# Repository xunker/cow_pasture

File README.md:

# The Cow Pasture: Various boards and add-ons for the Macintosh LC and variants

## [Cow-Flipper](cow-flipper/README.md)

An adapter to flip the LC internal SCSI port by 180-degrees so devices like the original BlueSCSI can be plugged in with the OEM cable.

## [Stealth Cow](stealth-cow)

Adapter for dual-disk-drive LCs, so they can have an internal BlueSCSI drive while keeping both floppy drives. A work-in-progess.

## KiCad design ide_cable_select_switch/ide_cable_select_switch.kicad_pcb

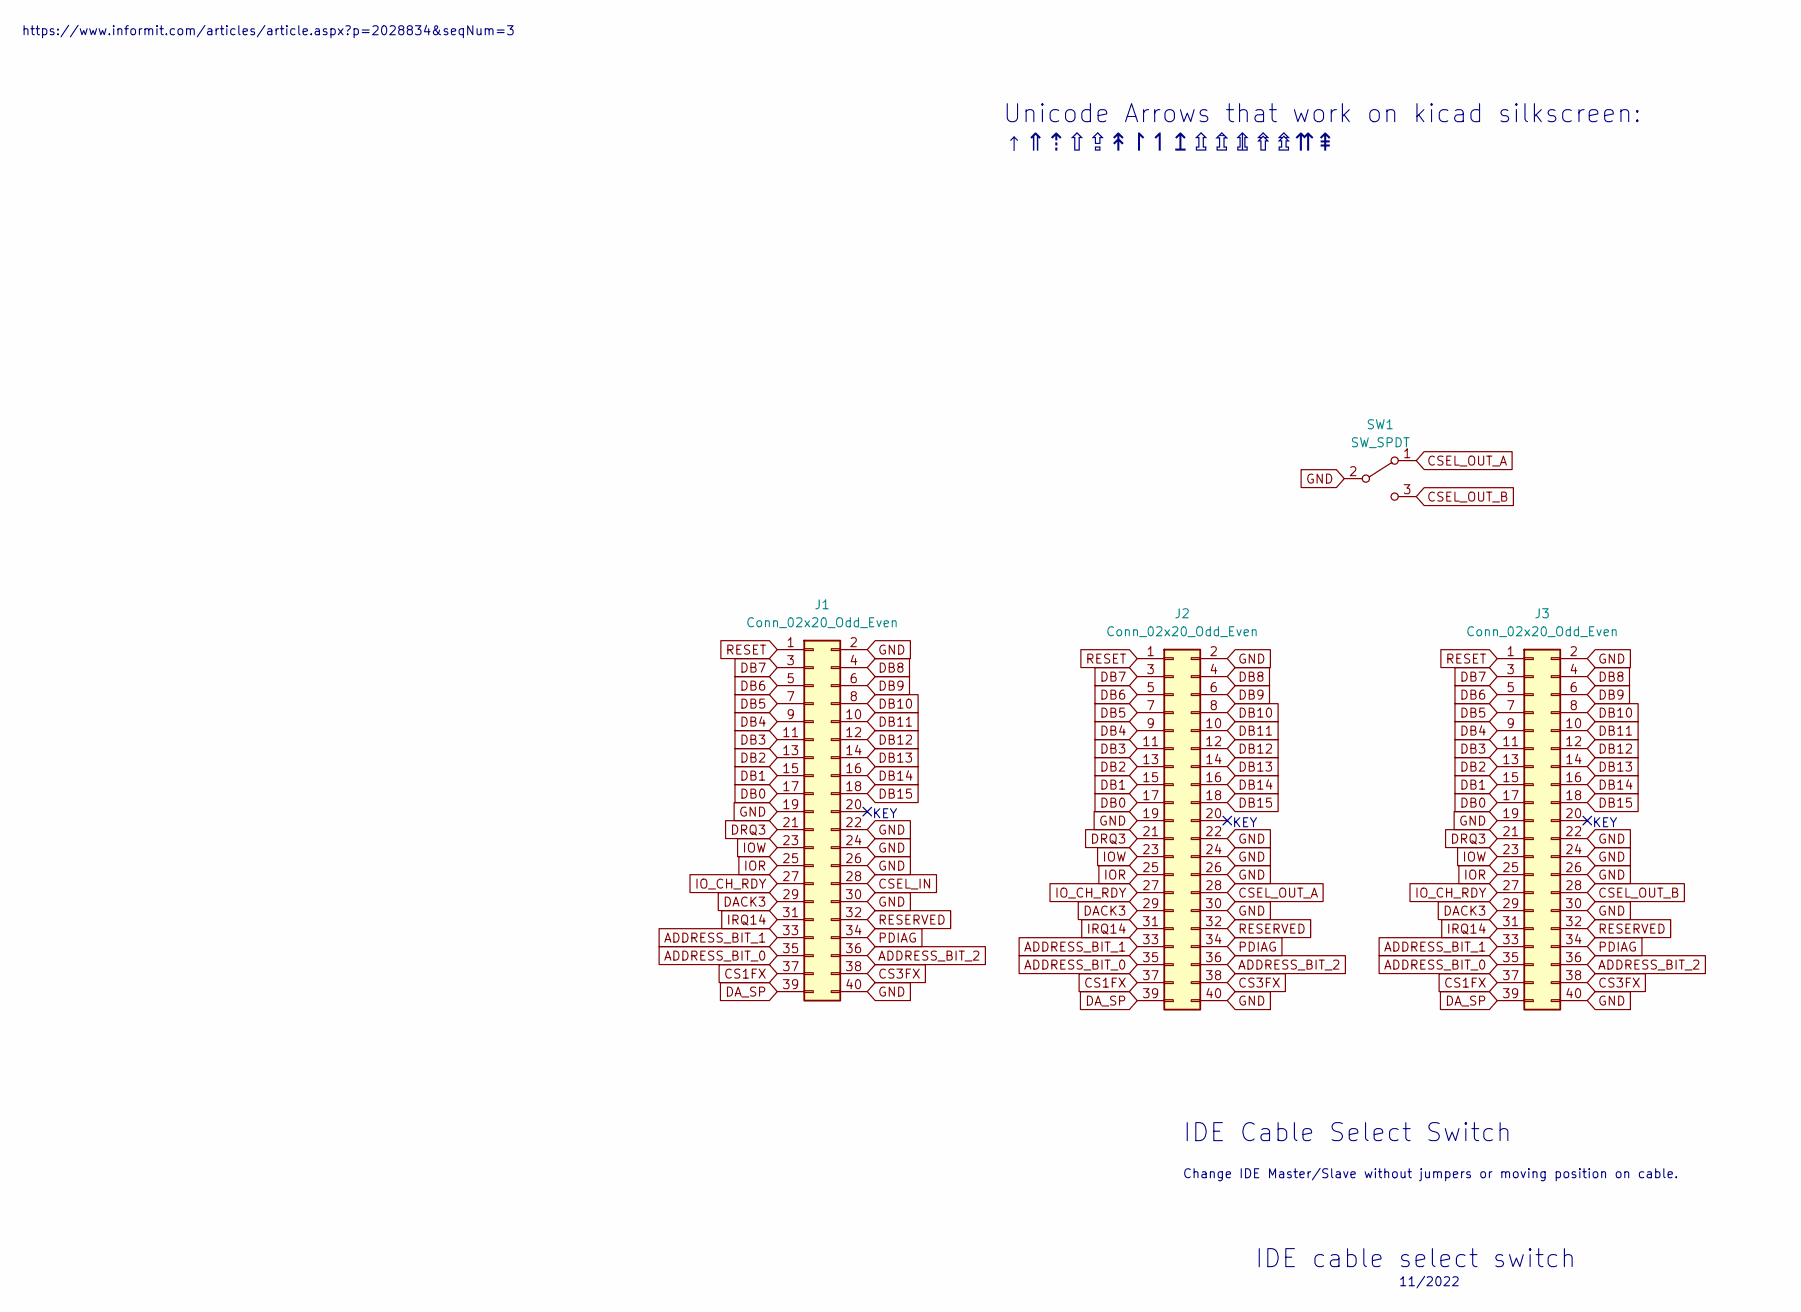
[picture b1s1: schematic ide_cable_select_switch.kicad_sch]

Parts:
J1, J2, J3: Conn_02x20_Odd_Even; IDE_ATA_Male_2x20_P2.54mm_Vertical_SMD
SW1: SW_SPDT; PinHeader_1x03_P2.54mm_Vertical

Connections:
ADDRESS_BIT_0: J1.35, J2.35, J3.35
ADDRESS_BIT_1: J1.33, J2.33, J3.33
ADDRESS_BIT_2: J1.36, J2.36, J3.36
CS1FX: J1.37, J2.37, J3.37
CS3FX: J1.38, J2.38, J3.38
CSEL_IN: J1.28
CSEL_OUT_A: J2.28, SW1.1 (A)
CSEL_OUT_B: J3.28, SW1.3 (C)
DACK3: J1.29, J2.29, J3.29
DA_SP: J1.39, J2.39, J3.39
DB0: J1.17, J2.17, J3.17
DB1: J1.15, J2.15, J3.15
DB2: J1.13, J2.13, J3.13
DB3: J1.11, J2.11, J3.11
DB4: J1.9, J2.9, J3.9
DB5: J1.7, J2.7, J3.7
DB6: J1.5, J2.5, J3.5
DB7: J1.3, J2.3, J3.3
DB8: J1.4, J2.4, J3.4
DB9: J1.6, J2.6, J3.6
DB10: J1.8, J2.8, J3.8
DB11: J1.10, J2.10, J3.10
DB12: J1.12, J2.12, J3.12
DB13: J1.14, J2.14, J3.14
DB14: J1.16, J2.16, J3.16
DB15: J1.18, J2.18, J3.18
DRQ3: J1.21, J2.21, J3.21
GND: J1.2, J1.19, J1.22, J1.24, J1.26, J1.30, J1.40, J2.2, J2.19, J2.22, J2.24, J2.26, J2.30, J2.40, J3.2, J3.19, J3.22, J3.24, J3.26, J3.30, J3.40, SW1.2 (B)
IOR: J1.25, J2.25, J3.25
IOW: J1.23, J2.23, J3.23
IO_CH_RDY: J1.27, J2.27, J3.27
IRQ14: J1.31, J2.31, J3.31
PDIAG: J1.34, J2.34, J3.34
RESERVED: J1.32, J2.32, J3.32
RESET: J1.1, J2.1, J3.1

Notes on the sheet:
KEY
Unicode Arrows that work on kicad silkscreen: ↑⇑⇡︎⇧⇪↟↾↿↥⇫⇬⇭⇮⇯⇈⇞
IDE cable select switch
IDE Cable Select Switch
Change IDE Master/Slave without jumpers or moving position on cable.
11/2022
https://www.informit.com/articles/article.aspx?p=2028834&seqNum=3

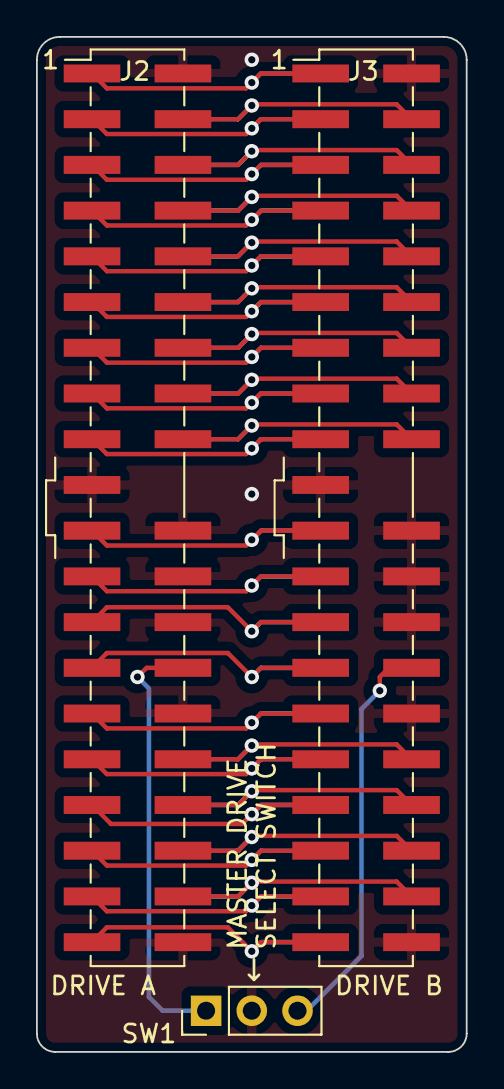
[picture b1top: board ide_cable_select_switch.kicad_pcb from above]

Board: 2 copper layers, 23.9 x 56.4 mm, 4 parts (1 on the bottom side), 34 nets.

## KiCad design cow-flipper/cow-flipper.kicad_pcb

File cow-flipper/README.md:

# Cow-Flipper

An adapter to flip the Macintosh LC internal SCSI port by 180-degrees so devices like the original BlueSCSI can be plugged in with the OEM cable.

## Get One

*Link TBA*

## Make One

The Gerber files you can use to fabricate your own boards can be found in the [gerber](gerber/) directory.

## Image Credit

The "cow head" image is based on "[Oh la vache!](https://openclipart.org/detail/306907/oh-la-vache)" by "j4p4n", from openclipart.org/

## License

Board design distributed under the terms of the [Creative Commons
Attribution-NonCommercial-ShareAlike 4.0 International (CC BY-NC-SA 4.0) License](https://creativecommons.org/licenses/by-nc-sa/4.0/).

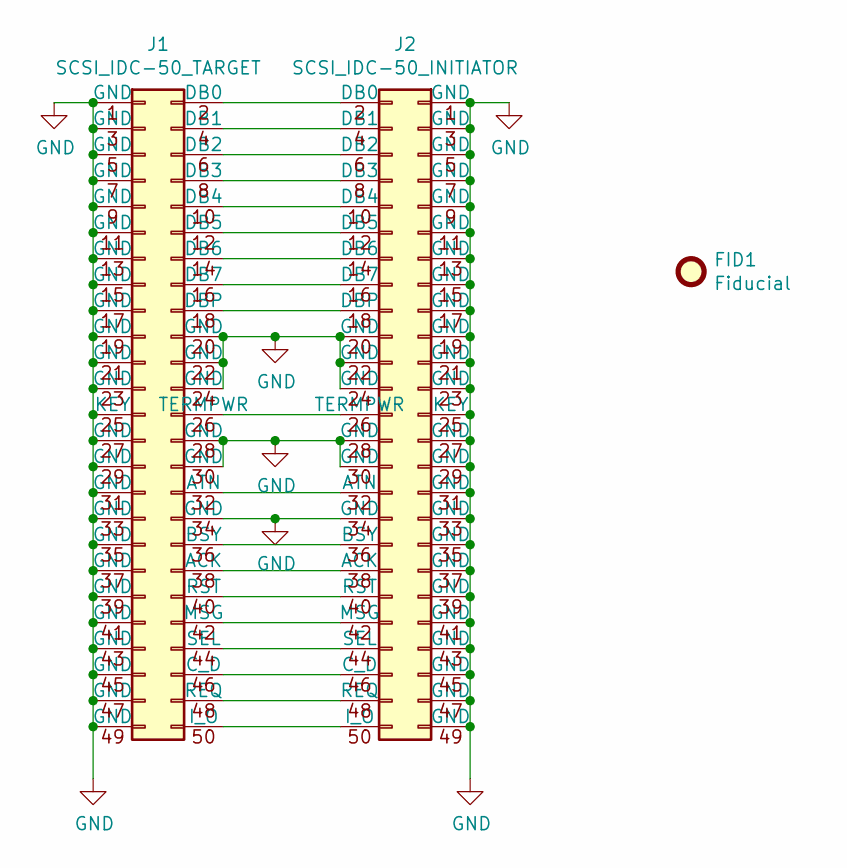
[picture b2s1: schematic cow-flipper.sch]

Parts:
FID1: Fiducial; cowhead_fsilk
J1: SCSI_IDC-50_TARGET; PinSocket_2x25_P2.54mm_Vertical
J2: SCSI_IDC-50_INITIATOR; idc-50-edge-male

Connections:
GND: J1.1 (GND), J1.3 (GND), J1.5 (GND), J1.7 (GND), J1.9 (GND), J1.11 (GND), J1.13 (GND), J1.15 (GND), J1.17 (GND), J1.19 (GND), J1.20 (GND), J1.21 (GND), J1.22 (GND), J1.23 (GND), J1.24 (GND), J1.25 (KEY), J1.27 (GND), J1.28 (GND), J1.29 (GND), J1.30 (GND), J1.31 (GND), J1.33 (GND), J1.34 (GND), J1.35 (GND), J1.37 (GND), J1.39 (GND), J1.41 (GND), J1.43 (GND), J1.45 (GND), J1.47 (GND), J1.49 (GND), J2.1 (GND), J2.3 (GND), J2.5 (GND), J2.7 (GND), J2.9 (GND), J2.11 (GND), J2.13 (GND), J2.15 (GND), J2.17 (GND), J2.19 (GND), J2.20 (GND), J2.21 (GND), J2.22 (GND), J2.23 (GND), J2.24 (GND), J2.25 (KEY), J2.27 (GND), J2.28 (GND), J2.29 (GND), J2.30 (GND), J2.31 (GND), J2.33 (GND), J2.34 (GND), J2.35 (GND), J2.37 (GND), J2.39 (GND), J2.41 (GND), J2.43 (GND), J2.45 (GND), J2.47 (GND), J2.49 (GND)
unnamed: J1.2 (DB0), J2.2 (DB0)
unnamed: J1.4 (DB1), J2.4 (DB1)
unnamed: J1.6 (DB2), J2.6 (DB2)
unnamed: J1.8 (DB3), J2.8 (DB3)
unnamed: J1.10 (DB4), J2.10 (DB4)
unnamed: J1.12 (DB5), J2.12 (DB5)
unnamed: J1.14 (DB6), J2.14 (DB6)
unnamed: J1.16 (DB7), J2.16 (DB7)
unnamed: J1.18 (DBP), J2.18 (DBP)
unnamed: J1.26 (TERMPWR), J2.26 (TERMPWR)
unnamed: J1.32 (ATN), J2.32 (ATN)
unnamed: J1.36 (BSY), J2.36 (BSY)
unnamed: J1.38 (ACK), J2.38 (ACK)
unnamed: J1.40 (RST), J2.40 (RST)
unnamed: J1.42 (MSG), J2.42 (MSG)
unnamed: J1.44 (SEL), J2.44 (SEL)
unnamed: J1.46 (C_D), J2.46 (C_D)
unnamed: J1.48 (REQ), J2.48 (REQ)
unnamed: J1.50 (I_O), J2.50 (I_O)

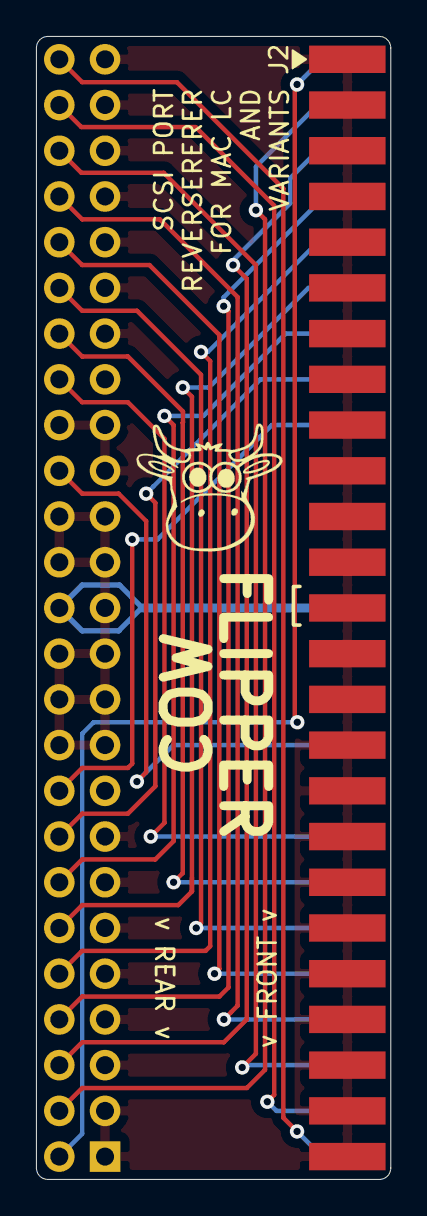
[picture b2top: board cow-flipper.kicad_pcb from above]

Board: 2 copper layers, 19.7 x 63.5 mm, 3 parts (1 on the bottom side), 20 nets.

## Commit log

2021-06-24 Initial commit of all; cow-flipper version is first version sent to fab
2021-06-24 Added CC-SA-NC lisence
2021-06-24 Renamed files, populated readme
2021-06-24 change link target to be readme instead of bare dir
2022-11-06 Initial commit of working IDE cable select switch
2022-11-06 Updated headers in to specific IDE header without pad for key pin
2022-11-06 Move ground vias now that key pins are not in the way
2022-11-06 Extend PCB below switch to help with unplugging leverage
2022-11-06 Added IDC key indicator to sinkscreen
2022-11-07 Add pads for external switch
2022-11-08 Remove extra switch pads; turn main switch in to 2.54 header so it can be used for both a fixed and remote switch using the same footprint.
2022-11-23 just ignore all zips
2022-11-23 previous fab changes
2022-11-23 New standalone component for UCC3916

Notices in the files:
ide_cable_select_switch/ide_cable_select_switch.kicad_pcb:
github.com/xunker ©2022
